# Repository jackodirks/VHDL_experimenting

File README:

This project is basically a huge VHDL experiment. This project is focused on only testbenching.

The project uses GHDL:
https://github.com/tgingold/ghdl
And gtkwave, but that should be in your repo's.        

Sources of information:
Usage of GHDL:
http://www.armadeus.com/wiki/index.php?title=How_to_make_a_VHDL_design_in_Ubuntu/Debian#Using_Xilinx_command_line_tools_for_shell_syntesis
http://ghdl.readthedocs.org/en/latest/index.html

Running happens using the Makefile in the project directory. Type `make` to make GHDL scan and process all VHDL files specified, type `make run` to run the testbench (implies `make`) and type `make simulate` to start gtkwave with the generated output file (implies `make run`).

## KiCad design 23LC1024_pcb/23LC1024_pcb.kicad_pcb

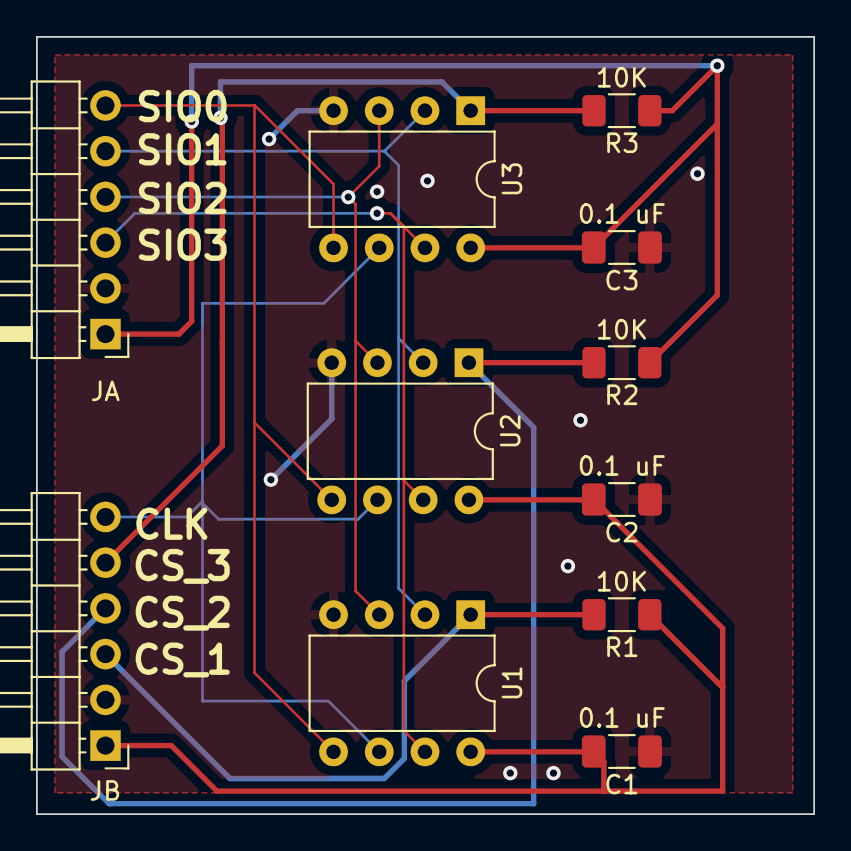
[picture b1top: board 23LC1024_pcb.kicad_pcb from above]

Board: 2 copper layers, 43.2 x 43.2 mm, 11 parts (0 on the bottom side), 10 nets.

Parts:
C1, C2, C3: 0.1 uF; C_1206_3216Metric_Pad1.33x1.80mm_HandSolder
JA: Conn_01x06_Male_JA; PinHeader_1x06_P2.54mm_Horizontal
JB: Conn_01x06_Male_JB; PinHeader_1x06_P2.54mm_Horizontal
R1, R2, R3: 10K; R_1206_3216Metric_Pad1.30x1.75mm_HandSolder
U1, U2, U3: 23LC1024-I/P; DIP-8_W7.62mm

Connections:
/CLK: JB.6 (CLK), U1.6 (SCK), U2.6 (SCK), U3.6 (SCK)
/CS_1: JB.3 (CS_1), R1.2, U1.1 (*CS)
/CS_2: JB.4 (CS_2), R2.2, U2.1 (*CS)
/CS_3: JB.5 (CS_3), R3.2, U3.1 (*CS)
/SIO0: JA.6 (SIO0), U1.5 (SI/SIO0), U2.5 (SI/SIO0), U3.5 (SI/SIO0)
/SIO1: JA.5 (SIO1), U1.2 (SO/SIO1), U2.2 (SO/SIO1), U3.2 (SO/SIO1)
/SIO2: JA.4 (SIO2), U1.3 (SIO2), U2.3 (SIO2), U3.3 (SIO2)
/SIO3: JA.3 (SIO3), U1.7 (*HOLD/SIO3), U2.7 (*HOLD/SIO3), U3.7 (*HOLD/SIO3)
BASYS3V3: C1.2, C2.2, C3.2, JA.1 (3V3), JB.1 (3V3), R1.1, R2.1, R3.1, U1.8 (VCC), U2.8 (VCC), U3.8 (VCC)
GND: C1.1, C2.1, C3.1, JA.2 (GND), JB.2 (GND), U1.4 (VSS), U2.4 (VSS), U3.4 (VSS)

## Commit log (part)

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2017-01-06 Removed obsolete and confusing runfile
2017-01-06 Makes the reset of the simple multishot timer async
2017-01-06 Extends the ss test and connects it to tb_main
2017-01-10 Removes hstr function from ss tb, adds libref instead
2017-01-11 Finishes the full seven segments test
2017-01-18 Adds the MIT license
2017-01-18 Adds some make instructions to the README
2017-01-24 Adds a make distclean option
2017-01-24 Adds the BENCHFLAGS var to make system
2017-01-24 Common testbench will now run
2017-01-24 Adds .o files to gitignore
2017-01-25 Implements a simple_multishot_timer test
2017-01-29 Moves uart tests to uart_tb
2017-01-30 Starts replacing magic values with named constants
2017-02-02 Removes the last magic numbers from uart_tb
2017-04-12 Adds an SPI folder, extends build system
2017-04-12 Adds the first steps of the architecture of SPI slave
2017-04-13 spi_slave: Adds debouncing for sclk, extends fsm implementation
2017-04-14 Changes SPI slave block philosophy, finishes FSM transitions
2017-04-20 Introduces a sife-like process to store SPI settings
2017-04-27 Finishes spi_slave implementation, no tests yet
2017-04-28 spi_slave: fixes slave select behaviour
2017-04-28 spi_slave: fixes input reading
2017-04-28 Revert "Renames button_to_single_pulse to static_debouncer"
    This reverts commit 52aa92cd82baa78bf7ebc2302e54a5e0dfe71bf4.
2017-04-28 uart_tb: makes sure main_{done success} change statements are hit
2017-04-28 Introduces a real static debouncer
2017-04-28 spi_slave: fixes behaviour
2017-04-28 Reworks the static debouncer
2017-04-29 Removes component usage troughout project
2017-05-01 Changes VHDL standard from 93 to 00
2017-05-01 spi_slave: debouncer now only generated if debounce_ticks > 0
2017-05-07 spi_slave: general cleanup
2018-07-29 Starts revisiting SPI slave
2018-08-21 Fixed clock finishing too early in UART tb
2018-08-21 SPI static slave fully tested
2018-08-21 Static SPI slave finished and tested for POL=PHA=0
2021-10-28 depp_slave: First non-tested version
2021-11-01 Create new bus test in vunit
2021-11-06 deppSlave: Hold internal bus active until DEPP is finished
2021-11-06 Add an intergration test for DEPP and bRAM
2021-11-28 deppSlave: Delay input because of clock domain
    Also release internal bus ASAP
2021-11-28 main_file: Remove rst from push_button
    push_button might ghost
2021-11-30 Introduce bus_demux
2021-12-26 bus_singleport_ram: Drive the slv2mst fault bit
2021-12-26 seven_seg_controller: Change cur_digit
    The old design would generate a warning because cur_digit could be
    higher than the amount of digits. This new design fixes this warning
2021-12-26 main_file.vhd: Incoporate demux, seven_segment_controller
2021-12-31 bus: Introduce remapping capabilities
2022-01-04 deppSlave: Introduce depp_to_bus
2022-02-06 Rework bus_singleport_ram
    This new implementation will garantuee proper function on Basys 2
2022-02-06 Resize bus to 32/32
2022-02-07 depp_slave: Save some cycles
2022-02-07 Add complete_system
2022-02-13 DeppSlave: Extend depp_slave_controller test
2022-02-15 Expand depp_slave test
2022-02-20 Readd complete_system
2022-03-05 depp_slave_controller: minmax check for depp_address
2022-03-06 Introduce depp_master c++ program
2022-03-17 Fix gitignore for depp_master
2022-09-18 23LC1024 PCB: Finish routing
2022-12-01 depp_tb_pkg: Use more generic types
2022-12-01 triple_23lc1024: Create and test triple_23lc1024_config
2022-12-01 23LC1024 simulation: Turn memory into variable
    This makes the simulation a lot faster
2022-12-01 triple_23lc1024_controller: 23LC1024 sim: Remove unused timings
2022-12-01 triple_23lc1024_controller: test: Cleanup
2022-12-03 Bus: Add burst flag
2022-12-11 triple_23lc1024_controller: tb: Prefer VU com over dbg signals
2022-12-24 triple_23lc1024_controller: Introduce rw via COM
2022-12-29 triple_23lc1024_writer: Fix order issue
2022-12-29 triple_23lc1024_{reader|writer}: Add fault signal
2022-12-31 triple_23lc1024_writer: Handle faults
2022-12-31 Introduce triple_23lc1024_cs_control
2022-12-31 triple_23lc1024: Dont use inout unless you have to
2023-01-02 triple_23lc1024_controller: Add writer
2023-01-03 bus_pkg: bus_map_constant: use for loop instead of others
    This fixes a synthesis warning.
2023-01-03 triple_23lc1024_{reader|writer}: Limit range of count
    This actually generates less hardware
2023-01-03 main_file: Add spimem, remap bmem
2023-01-03 triple_23lc1024_config: explicitly check cs_timer_done = '1'
    Synthesis does not like to implicity typecast std_logic to boolean
2023-01-03 triple_23lc1024: Fix CS selection issue
    Address was not clocked in so that the selected chip changed whenever
    the bus changed. This is fixed now
2023-01-06 Touch up simple_multishot_timer
2023-01-06 Remove two_brams test
    Slow tests who only retest what is tested elsewhere
2023-01-06 Add simulated_bus_memory
2023-01-06 Add simulated_depp_master
2023-02-05 Redo bus_demux
2023-02-05 Introduce bus_arbiter
2023-03-01 Introduce mips32_pipeline_instructionDecode
2023-03-01 Add mips32_debug_controller
2023-03-09 Introduce mips32_alu
2023-03-09 Introduce mips32_pipeline_execute
2023-03-12 Introduce mips32_pipeline_memory
2023-03-31 mips32_pipeline_instructionDecode: Add regAddress{A|B}
2023-03-31 Introduce mips32_pipeline_forwarding_unit
2023-04-01 mips32_pipeline: implement forwarding unit
2023-04-01 mips32_pipeline_simulated_memory_pkg: Add procedure write_file_to_address
2023-04-02 mips32: regAddressA -> rsAddress
2023-04-02 mips32: regAddressB -> rtAddress
2023-04-02 mips32_pipeline_simulated_memory: Add offset_address
2023-04-02 mips32_processor: Add lui instruction
2023-04-02 Add hal project
2023-04-05 mips32_pipeline: add Delayed looped add test
2023-04-20 Introduce mips32_mem2bus
2023-05-07 Move alu, registerFile into pipeline
2023-05-07 Remove simulation Makefile
2023-05-13 bus_arbiter: Fix going from mst 2 to 0
2023-05-13 mips32_pipeline: instruction is of instruction_type
2023-05-13 Introduce mips32_processor.vhd
2023-05-13 simulated_depp_master_pkg: Add write_file_to_address
2023-05-13 Introduce processor into main_file
2023-05-14 use *.bus_pkg => use *.bus_pkg.all
    Synthesis does not like the no-suffix solution
2023-05-30 run.py: Follow deprication warning
2023-06-02 bus_arbiter: Fix latch-by-technicalilty sitation
2023-06-04 Introduce uart_bus_master_baudgen
2023-06-09 Introduce uart_bus_master_rx
2023-06-09 Introduce uart_bus_master
2023-06-09 Reimplement uart_bus_master
2023-06-16 mips32_pipeline_writeBack: Fix sensitivity list
2023-06-16 main_file_tb: Set baud_rate to 1128000
2023-06-16 Increase speed to 2000000 baud
2023-06-16 Revert "triple_23LC1024_controller: Remove time-based constants"
    This reverts commit 786fb18ccd3a98fdfb3f8264630958c7a42bf4b9.
2023-06-17 alu: Add unsigned subtract
2023-06-18 Mips32: Implement bne
2023-06-18 Mips32: Add a bunch of R-type instructions
2023-06-18 Mips32: Implement jal, jr
2023-06-19 Mips32 instructionDecode: Dont repeat when ignoreCurrentInstruction
2023-06-20 triple_23lc1024_controller: Split bus_handling for timing
2023-06-22 rename write_mask to byte_mask
2023-06-29 Introduce triple_23lc1024_bus_parser
2023-06-29 triple_23lc1024_bus_parser: Temporarily forbid bytemasks /= 1111
2023-06-29 Test with 8ns clock
2023-06-29 triple_23lc1024_writer: Allow arbitrary write size
2023-07-01 Revert "triple_23lc1024_bus_parser: Temporarily forbid bytemasks /= 1111"
    This reverts commit 1263675b0bf2f055391913bc7c731358afa1fdc7.
2023-07-01 triple_23LC1024_controller_tb: Test partial write
2023-07-01 mips32: Implement lui, sra into ALU
2023-07-08 bus_pkg: Clarify slave valid rules
2023-07-08 mips32: Introduce coprocessor 0
2023-07-10 mips32_pipeline_instructionDecode: Introduce {rs,rt,rd}Address_buf
2023-07-10 mips32_processor: cpz reg 1 is clk_frequency
2023-07-11 mips32_processor: Use loadHazardDetector
2023-07-11 mips32_processor: Wire rdAddress trough the pipeline
2023-07-15 Inject bubble because of cop0ToReg
    Also fixes an issue where bubble injection did not always happen. This
    introduces a performance issue where there might be too many bubbles
    (addui after lw, under certain circumstances), but we just take that for
    now.
2023-07-19 mips32: Add idexRegister
2023-07-20 mips32_processor: Move regfile out of instructionDecode
2023-07-20 mips32_pipeline_execute: Get rid of justBranched signal
    It was very akward and can be solved via instructionFetch
2023-07-23 Mips32: Introduce utils directory
2023-07-23 mips32_pkg: Set nop to sll $0,$0,$0
    As is convention
2023-07-23 move mips32_registerFile to pipeline
2023-07-25 mips32: introduce pipeline_memwbRegister
2023-07-30 mips32_pipeline_registerFile: Add ext port
2023-07-30 Make mips32 register file accessable from UART master
2023-07-30 mips32: Remove ALUSrc
2023-08-07 mips32: Implement lb, lh, lbu, lhu, sb and sh
2023-08-13 Introduce mips32_icache
2023-08-13 mips32: Use iCache
2023-09-16 Project: Remove rules.mk files
2023-09-16 Introduce dcache_bank
2023-09-16 Introduce vivado_tcl
2023-09-18 mips32: Intergrate dcache
2023-09-19 mips32_processor: mem2bus: Introduce dcache_updating_from_bus
    This improves preformance of router
2023-09-21 mips32_dcache: Make sure addressOut is never set twice
2023-09-21 mips32_icache_bank: tag_size_log2b -> tag_size
2023-09-24 triple_23lc1024_controller: Move reorder_nibbles into testbench
    Strictly speaking reorder nibbles is not necessary, since it does not
    matter that the data is stored in some weird order because it is read
    back in that same order. Therefore, removed from production, moved into
    testbench
2023-09-26 triple_23lc1024_controller: Allow any contiguous byte mask
2023-09-28 mips32: Introduce lwl/lwr
2023-10-05 Mips32: Implement swl/swr
2023-10-05 mips32_mem2bus: Optimize timing on stall detection
2023-10-11 build.tcl: Penalize placement for faster routing
2023-10-11 mips32: Remove magic numbers for COP0 instructions
2023-10-15 triple_23lc1024_bus_parser: Fix tests and bug with bytemask 0001
2023-10-15 hal: Reintroduce bubblesort program
2023-10-15 Mips32: implement BEQL
2023-10-15 Mips32: Implement bgez
2023-10-17 mips32 forwarding unit: forward 0 on address 0
    This greatly helps the router
2023-10-20 mips32: Implement BGEZAL
2023-10-20 Mips32: Add blez, bgezl support
2023-10-20 Mips32: Implement bgtz
2023-10-20 mips32: Implement bltz
2023-10-21 mips32: Introduce bgezal forwarding test
2023-10-21 mips32: Introduce regWrite_override
    This replaces write_on_branch and has_branched to save an and in the
    writeback stage
2023-10-21 mips32: Implement bnel
2023-10-22 vivado_tcl: Drop clockspeed to 100 MHz (was 125 MHz)
2023-10-22 Mips32: Implement jalr, mark JR.HB, JALR.HB as implemented
    The latter two need no special attention right now, as all hazards are
    automatically resolved.
2023-10-28 mips32 executeControlWord: Get rid of use_immidiate
2023-10-28 Mips32: Implement ori
2023-11-05 mips32: Forward entire instruction to control
2023-11-10 riscv32: introduce instructionDecode
2023-11-11 riscv32_processor: introduce alu, shifter
2023-11-11 riscv32_processor: Introduce riscv32_pipeline_execute
2023-11-12 riscv32_processor: Introduce riscv32_pipeline_writeback
2023-11-12 riscv32_processor: instroduce forwarding_unit
2023-11-12 riscv32_processor: Introduce registerFile
2023-11-12 riscv32_processor: Introduce exmemRegister
2023-11-12 riscv32_processor: Introduce memwbRegister
2023-11-12 riscv32_processor: Introduce dcache
2023-11-12 riscv32_processor: Introduce icache
2023-11-12 riscv32_processor: Introduce bus_slave, CP0, if2bus and mem2bus
2023-11-12 Introduce riscv32_pipeline.vhd
2023-11-17 riscv32_pipeline_memory: Fix alignment/bytemask for sh, sb
2023-11-17 riscv32_dcache: Assume any request to be word aligned
2023-11-18 Intergrate riscv32 into main_file
2023-11-18 Introduce minimal-riscv-hal
2023-11-21 Remove seven_seg_controller
2023-11-23 Introduce configurable_multishot_timer
2023-12-25 Introduce generic_fifo
2023-12-25 Introduce uart_bus_slave_writer
2023-12-27 Introduce uart_bus_slave
2023-12-28 uart_bus_slave: Implement global reset
2023-12-29 Turn uart_master into flashing only
2023-12-29 uart_bus_slave: Fix bug where first bit of byte was ignored
2023-12-31 riscv-hal: Larger PoC
2024-01-02 uart_bus_master: Refactor
